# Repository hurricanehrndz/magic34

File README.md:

# Magic34

Custom 34 key keyboard that feels like magic!

![magic34 PCB][magic34pcb]

## Design

More info coming soon!

## Firmware

CI builds everything in `build.yaml`. Flash `settings_reset` on every board
before switching between these setups:

- Without a dongle: `magic34_left` (central) and `magic34_right`.
- With a USB dongle: `magic34_dongle`, `magic34_left_peripheral`, and
  `magic34_right`. The dongle pairs with both halves on its own and shows up
  on the host as a USB keyboard.

The dongle build also works on cheap nice!nano clones that lack the 32 kHz
crystal and DC/DC inductors. The halves run on battery and need DC/DC, so use
genuine nice!nanos for them.

[magic34pcb]: images/magic34.png

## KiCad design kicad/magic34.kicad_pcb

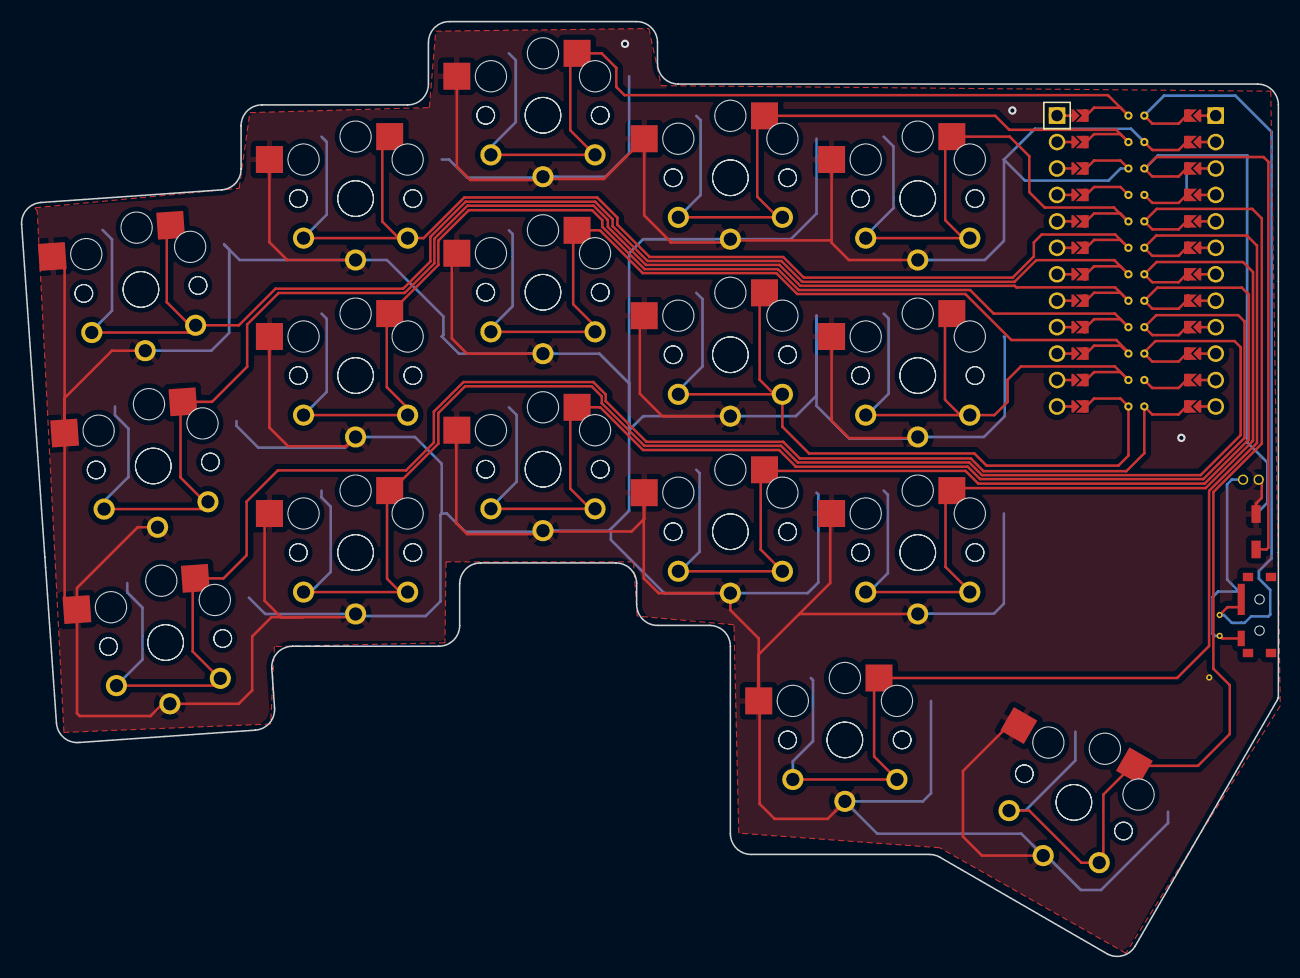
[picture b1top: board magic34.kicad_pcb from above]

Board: 2 copper layers, 120.7 x 89.8 mm, 35 parts (0 on the bottom side), 18 nets.

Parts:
MCU1: ProMicro
S1, S2, S3, S4, S5, S6, S7, S8, S9, S10, S11, S12, S13, S14, S15, S16, S17, S18, S19, S20, S21, S22, S23, S24, S25, S26, S27, S28, S29, S30, S31, S32, S33, S34: PG1350

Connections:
GND: MCU1.2, MCU1.21, MCU1.22, S1.2, S2.2, S3.2, S4.2, S5.2, S6.2, S7.2, S8.2, S9.2, S10.2, S11.2, S12.2, S13.2, S14.2, S15.2, S16.2, S17.2, S18.2, S19.2, S20.2, S21.2, S22.2, S23.2, S24.2, S25.2, S26.2, S27.2, S28.2, S29.2, S30.2, S31.2, S32.2, S33.2, S34.2
P0: MCU1.23, S23.1, S24.1
P1: MCU1.24, S17.1, S18.1
P2: MCU1.20, S29.1, S30.1
P3: MCU1.19, S11.1, S12.1
P4: MCU1.18, S5.1, S6.1
P5: MCU1.17, S3.1, S4.1
P6: MCU1.16, S9.1, S10.1
P7: MCU1.15, S15.1, S16.1
P8: MCU1.14, S27.1, S28.1
P9: MCU1.13, S21.1, S22.1
P10: MCU1.12, S1.1, S2.1
P14: MCU1.10, S7.1, S8.1
P15: MCU1.9, S13.1, S14.1
P18: MCU1.8, S19.1, S20.1
P19: MCU1.7, S25.1, S26.1
P20: MCU1.6, S31.1, S32.1
P21: MCU1.5, S33.1, S34.1

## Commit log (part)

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2023-01-10 Initial commit
    This commit includes ergogen v3 input and kicad files.
2023-01-11 Add zmk config for magic34
2023-01-11 Add LICENSE
2023-01-11 Fix zmk build via actions
2023-01-11 Fix typo in devicetree file
2023-01-11 Fix missing parentheses
2023-01-11 Fix typo
2023-01-11 Fix malformed conf
2023-01-11 Fix caps key
2023-01-11 Fix bt maps
2023-01-12 Fix up and down direction keys
2023-01-12 Add PCB image of magic34
2023-01-19 Fix uncomfortable key positions
2023-02-06 Better compatibility
2023-02-08 Produce settings reset
2025-02-23 Adding MEH
2026-01-05 Update board name
